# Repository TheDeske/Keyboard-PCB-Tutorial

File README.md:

# Keyboard PCB Tutorial
 1st step

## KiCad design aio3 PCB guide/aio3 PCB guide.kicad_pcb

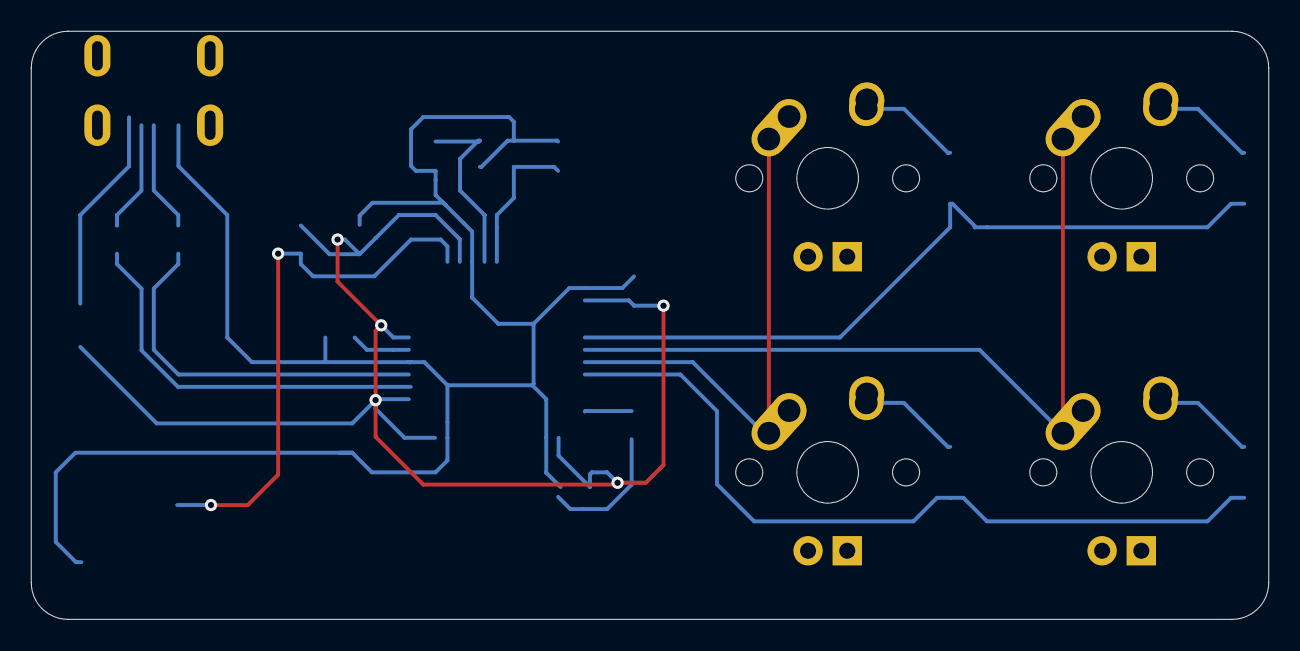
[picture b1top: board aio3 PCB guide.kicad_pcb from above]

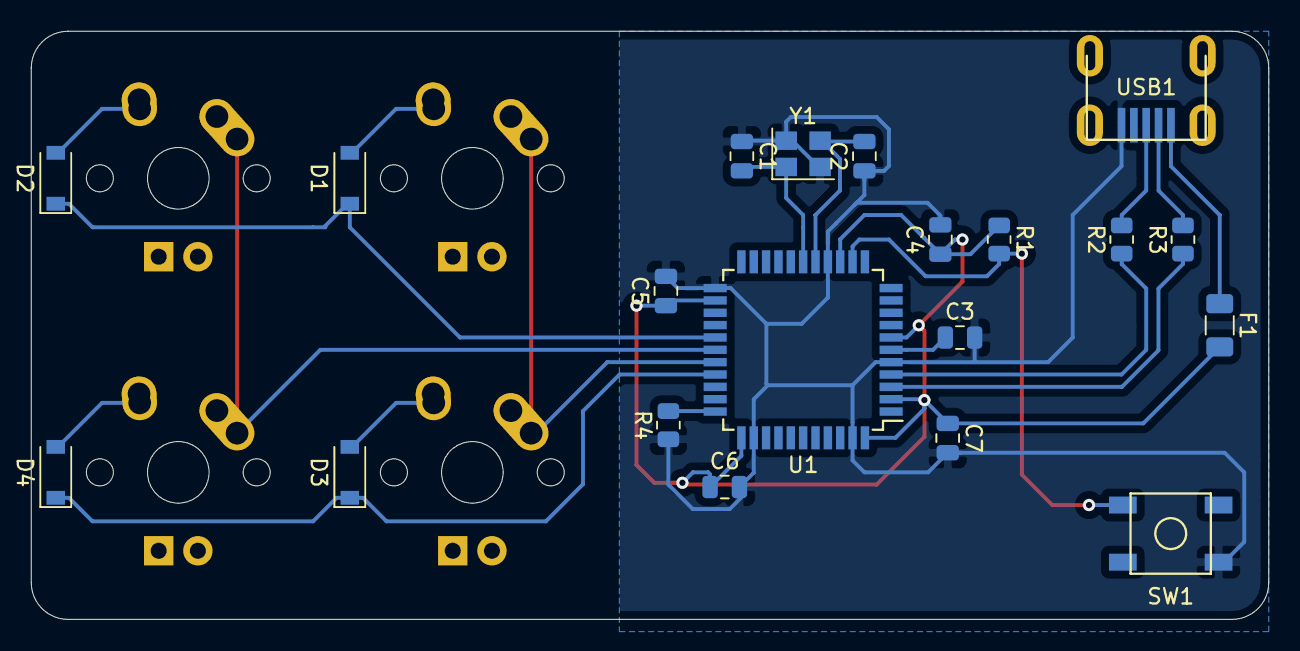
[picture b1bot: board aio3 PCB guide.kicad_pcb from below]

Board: 2 copper layers, 80.2 x 38.1 mm, 24 parts (20 on the bottom side), 20 nets.

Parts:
C1, C2: 22pf; C_0805_2012Metric
C3: 1uf; C_0805_2012Metric
C4, C5, C6: 0.1uf; C_0805_2012Metric
C7: 10uf; C_0805_2012Metric
D1, D2, D3, D4: D_Small; D_SOD-123
F1: 500mA; Fuse_1206_3216Metric
MX1, MX2, MX3, MX4: MX-NoLED; MX-1U
R1, R4: 10k; R_0805_2012Metric
R2, R3: 22; R_0805_2012Metric
SW1: SW_Push; SKQG-1155865
U1: ATmega32U4-AU; TQFP-44_10x10mm_P0.8mm
USB1: Molex-0548190589
Y1: 16mhz; Crystal_SMD_3225-4Pin_3.2x2.5mm

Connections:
+5V: C4.1, C5.1, C6.1, C7.1, F1.2, R1.1, U1.2, U1.7, U1.14, U1.24, U1.34, U1.44
COL0: MX1.1, MX3.1, U1.29
COL1: MX2.1, MX4.1, U1.28
D+: R2.2, USB1.3
D-: R3.2, USB1.4
GND: C1.1, C2.1, C3.2, C4.2, C5.2, C6.2, C7.2, R4.1, SW1.1, U1.5, U1.15, U1.23, U1.35, U1.43, USB1.1, Y1.2, Y1.4
unnamed: C1.2, U1.17, Y1.1
unnamed: C2.2, U1.16, Y1.3
unnamed: C3.1, U1.6
unnamed: D1.2, MX1.2
unnamed: D2.2, MX2.2
unnamed: D3.2, MX3.2
unnamed: D4.2, MX4.2
unnamed: R1.2, SW1.2, U1.13
unnamed: R2.1, U1.4
unnamed: R3.1, U1.3
unnamed: R4.2, U1.33
ROW0: D1.1, D2.1, U1.27
ROW1: D3.1, D4.1, U1.30
VCC: F1.1, USB1.5

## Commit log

2021-01-23 Initialised Project
2021-01-23 Add submodules
2021-01-23 Added footprint libraries
2021-01-23 Assigned footprints
2021-01-23 Physical layout down
2021-01-24 Stuff done
2021-01-24 PCB routed
2021-01-24 Finished PCB
2021-01-24 DRC complete (kinda)
2021-01-24 Finished
